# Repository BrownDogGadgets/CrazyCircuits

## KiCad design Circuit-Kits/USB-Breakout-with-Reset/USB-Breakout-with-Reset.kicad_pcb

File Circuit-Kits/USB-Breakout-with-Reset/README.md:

# USB-Breakout-with-Reset v1.0

Rewire Circuit Kit, Brown Dog Gadgets, 11/19/16

Circuit kit module to break out USB + and - signals, along with a RESET pushbutton, to program Rewire Circuit microcontrollers in place. 

\newpage

|Refdes|Qty|Description|Digikey Number|
|------|---|-----------|--------------|
|C1|1|CAP CER 1UF 16V X7R RADIAL|445-8614-ND|
|D1,D2|2|DIODE ZENER 3.6V 1W DO41|BZX85C3V6-ND|
|J1|1|USB MICRO-B RECEPTACLE 5PIN SMT|609-4616-1-ND|
|R1|1|RES 1.5K OHM 1/2W 5% CF MINI|S1.5KHCT-ND|
|R2,R3|2|RES 66.5 OHM 1/4W 1% AXIAL|66.5XBK-ND|
|SW1|1|SWITCH TACTILE SPST-NO 0.05A 24V|SW400-ND|

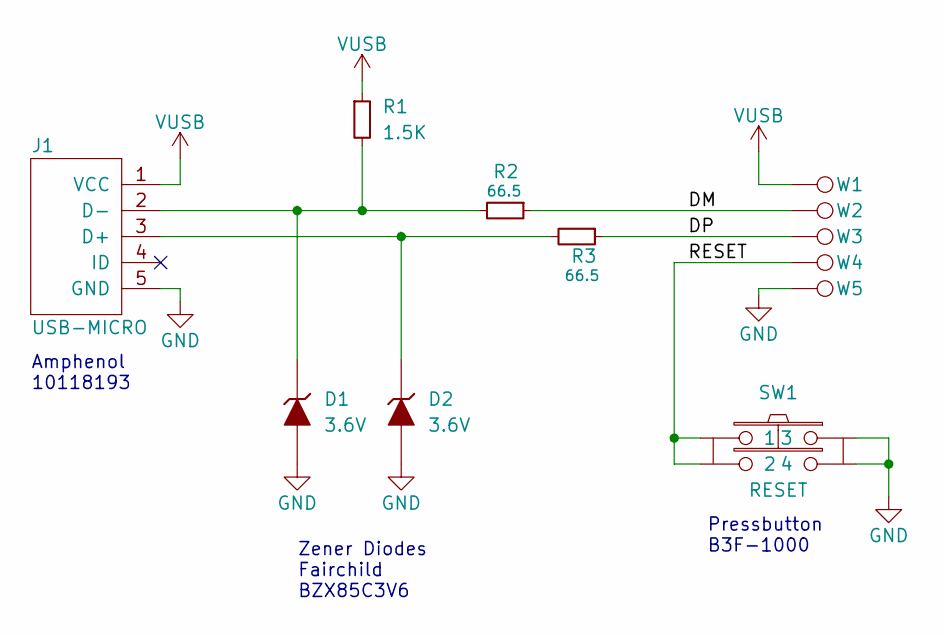
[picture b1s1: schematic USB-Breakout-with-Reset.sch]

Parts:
D1, D2: 3.6V; DIODE-DO-41
J1: USB-MICRO; CONN-USB-MICRO-B-AMPHENOL-10118193-0001LF
R1: 1.5K; RES-CARBONFILM-7MM
R2, R3: 66.5; RES-CARBONFILM-7MM
SW1: RESET; SWITCH-OMRON-MOMENTARY-TH-B3F-10XX
W1, W2, W3, W4, W5: TEST_1P; STANDALONE-LEGO-HOLE-PLATED

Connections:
/DM: R2.1, W2.1
/DP: R3.1, W3.1
/RESET: SW1.1, SW1.2, W4.1
GND: D1.2 (A), D2.2 (A), J1.5 (GND), SW1.3, SW1.4, W5.1
unnamed: D1.1 (K), J1.2 (D-), R1.2, R2.2
unnamed: D2.1 (K), J1.3 (D+), R3.2
VUSB: J1.1 (VCC), R1.1, W1.1

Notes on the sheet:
Zener Diodes Fairchild BZX85C3V6
Amphenol 10118193
Pressbutton B3F-1000

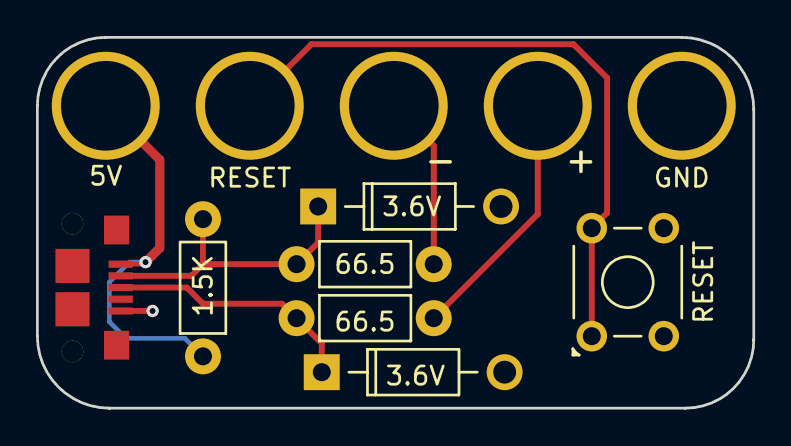
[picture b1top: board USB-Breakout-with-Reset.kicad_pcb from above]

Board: 2 copper layers, 39.8 x 20.6 mm, 12 parts (0 on the bottom side), 7 nets.

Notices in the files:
Circuit-Kits/USB-Breakout-with-Reset/USB-Breakout-with-Reset.kicad_pcb:
All Rights Reserved
